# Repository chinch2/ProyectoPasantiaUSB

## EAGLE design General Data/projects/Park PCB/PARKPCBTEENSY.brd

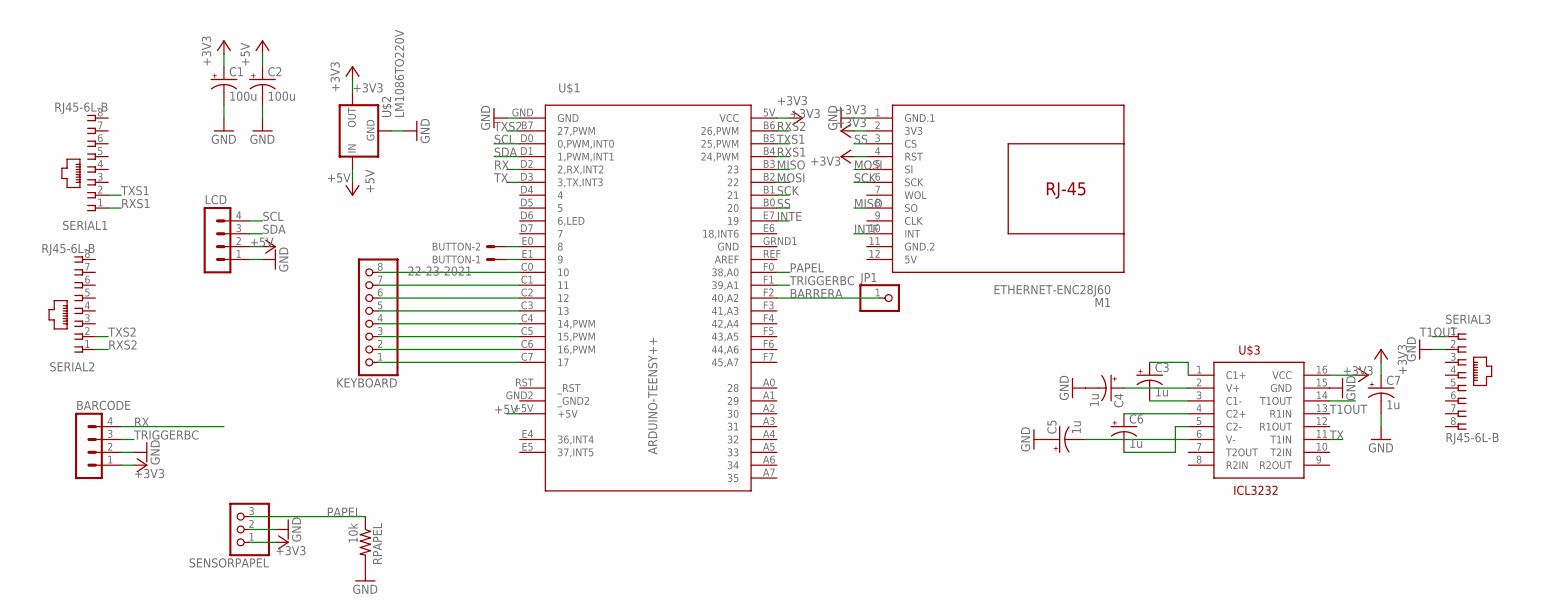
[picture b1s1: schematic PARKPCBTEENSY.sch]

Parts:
BARCODE: MA04-1
BUTTON: 22-23-2021
C1, C2: 100u; B45181B
C3, C4, C5, C6, C7: 1u; B45181B
JP1: PINHD-1X1; 1X01
KEYBOARD: PINHD-1X8BIG; 1X08-BIG
LCD: MA04-1
M1: ETHERNET-ENC28J60
RPAPEL: 10k; 0309/12
SENSORPAPEL: PINHD-1X3; 1X03
SERIAL1, SERIAL2, SERIAL3: RJ45-6L-B; RJ45-NO-SHIELD
U$1: ARDUINO-TEENSY++; TEENSY++
U$2: LM1086TO220V; TO220S
U$3: ICL3232; DIL16

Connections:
5V: M1.12 (5V)
+3V3: BARCODE.1, C1.+, C7.+, M1.2 (3V3), M1.4 (RST), SENSORPAPEL.1, U$1.5V (VCC), U$2.2 (OUT), U$3.16 (VCC)
+5V: C2.+, LCD.2, U$1.+5V, U$2.3 (IN)
BARRERA: JP1.1, U$1.F2 (40,A2)
GND: BARCODE.2, C1.-, C2.-, C4.-, C5.+, C7.-, LCD.1, M1.1 (GND.1), RPAPEL.2, SENSORPAPEL.2, SERIAL3.2, U$1.GND, U$1.GRND1 (GND), U$2.1 (GND), U$3.15 (GND)
GND.2: M1.11 (GND.2)
INTE: M1.10 (INT), U$1.E7 (19)
MISO: M1.8 (SO), U$1.B3 (23)
MOSI: M1.5 (SI), U$1.B2 (22)
unnamed: BUTTON.1, U$1.E1 (9)
unnamed: BUTTON.2, U$1.E0 (8)
unnamed: KEYBOARD.1, U$1.C7 (17)
unnamed: KEYBOARD.2, U$1.C6 (16,PWM)
unnamed: KEYBOARD.3, U$1.C5 (15,PWM)
unnamed: KEYBOARD.4, U$1.C4 (14,PWM)
unnamed: KEYBOARD.5, U$1.C3 (13)
unnamed: KEYBOARD.6, U$1.C2 (12)
unnamed: KEYBOARD.7, U$1.C1 (11)
unnamed: KEYBOARD.8, U$1.C0 (10)
unnamed: C3.+, U$3.1 (C1+)
unnamed: C4.+, U$3.2 (V+)
unnamed: C3.-, U$3.3 (C1-)
unnamed: C6.+, U$3.4 (C2+)
unnamed: C6.-, U$3.5 (C2-)
unnamed: C5.-, U$3.6 (V-)
PAPEL: RPAPEL.1, SENSORPAPEL.3, U$1.F0 (38,A0)
RX: BARCODE.4, U$1.D2 (2,RX,INT2)
RXS1: SERIAL1.1, U$1.B4 (24,PWM)
RXS2: SERIAL2.1, U$1.B6 (26,PWM)
SCK: M1.6 (SCK), U$1.B1 (21)
SCL: LCD.4, U$1.D0 (0,PWM,INT0)
SDA: LCD.3, U$1.D1 (1,PWM,INT1)
SS: M1.3 (CS), U$1.B0 (20)
T1OUT: SERIAL3.1, U$3.14 (T1OUT)
TRIGGERBC: BARCODE.3, U$1.F1 (39,A1)
TX: U$1.D3 (3,TX,INT3), U$3.11 (T1IN)
TXS1: SERIAL1.2, U$1.B5 (25,PWM)
TXS2: SERIAL2.2, U$1.B7 (27,PWM)
_GND2: U$1.GND2 (_GND2)

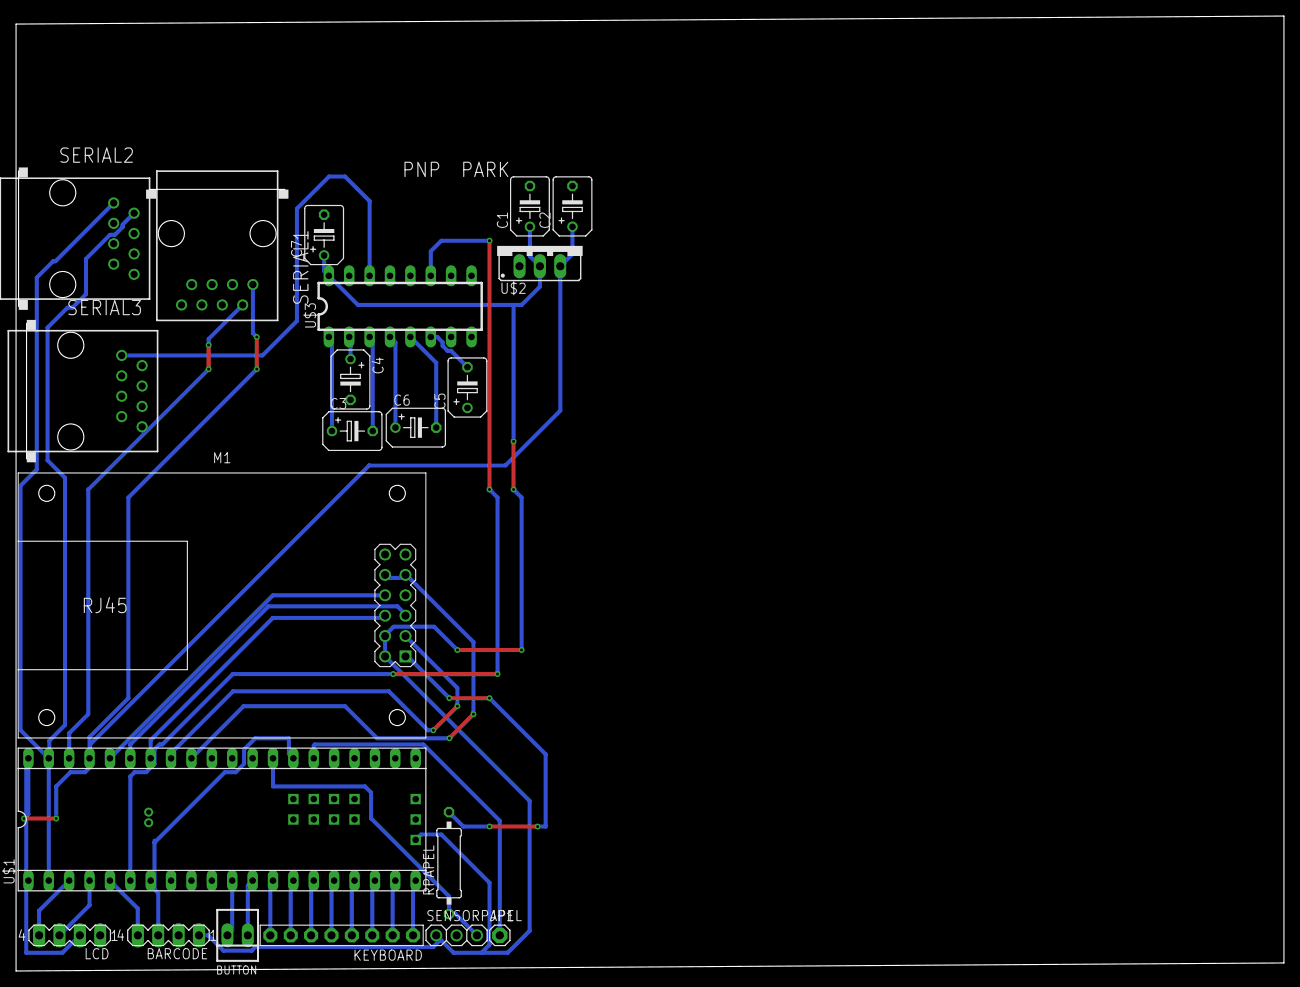
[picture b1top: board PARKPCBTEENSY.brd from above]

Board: 2 copper layers, 158.0 x 119.0 mm, 21 parts (0 on the bottom side), 36 nets.

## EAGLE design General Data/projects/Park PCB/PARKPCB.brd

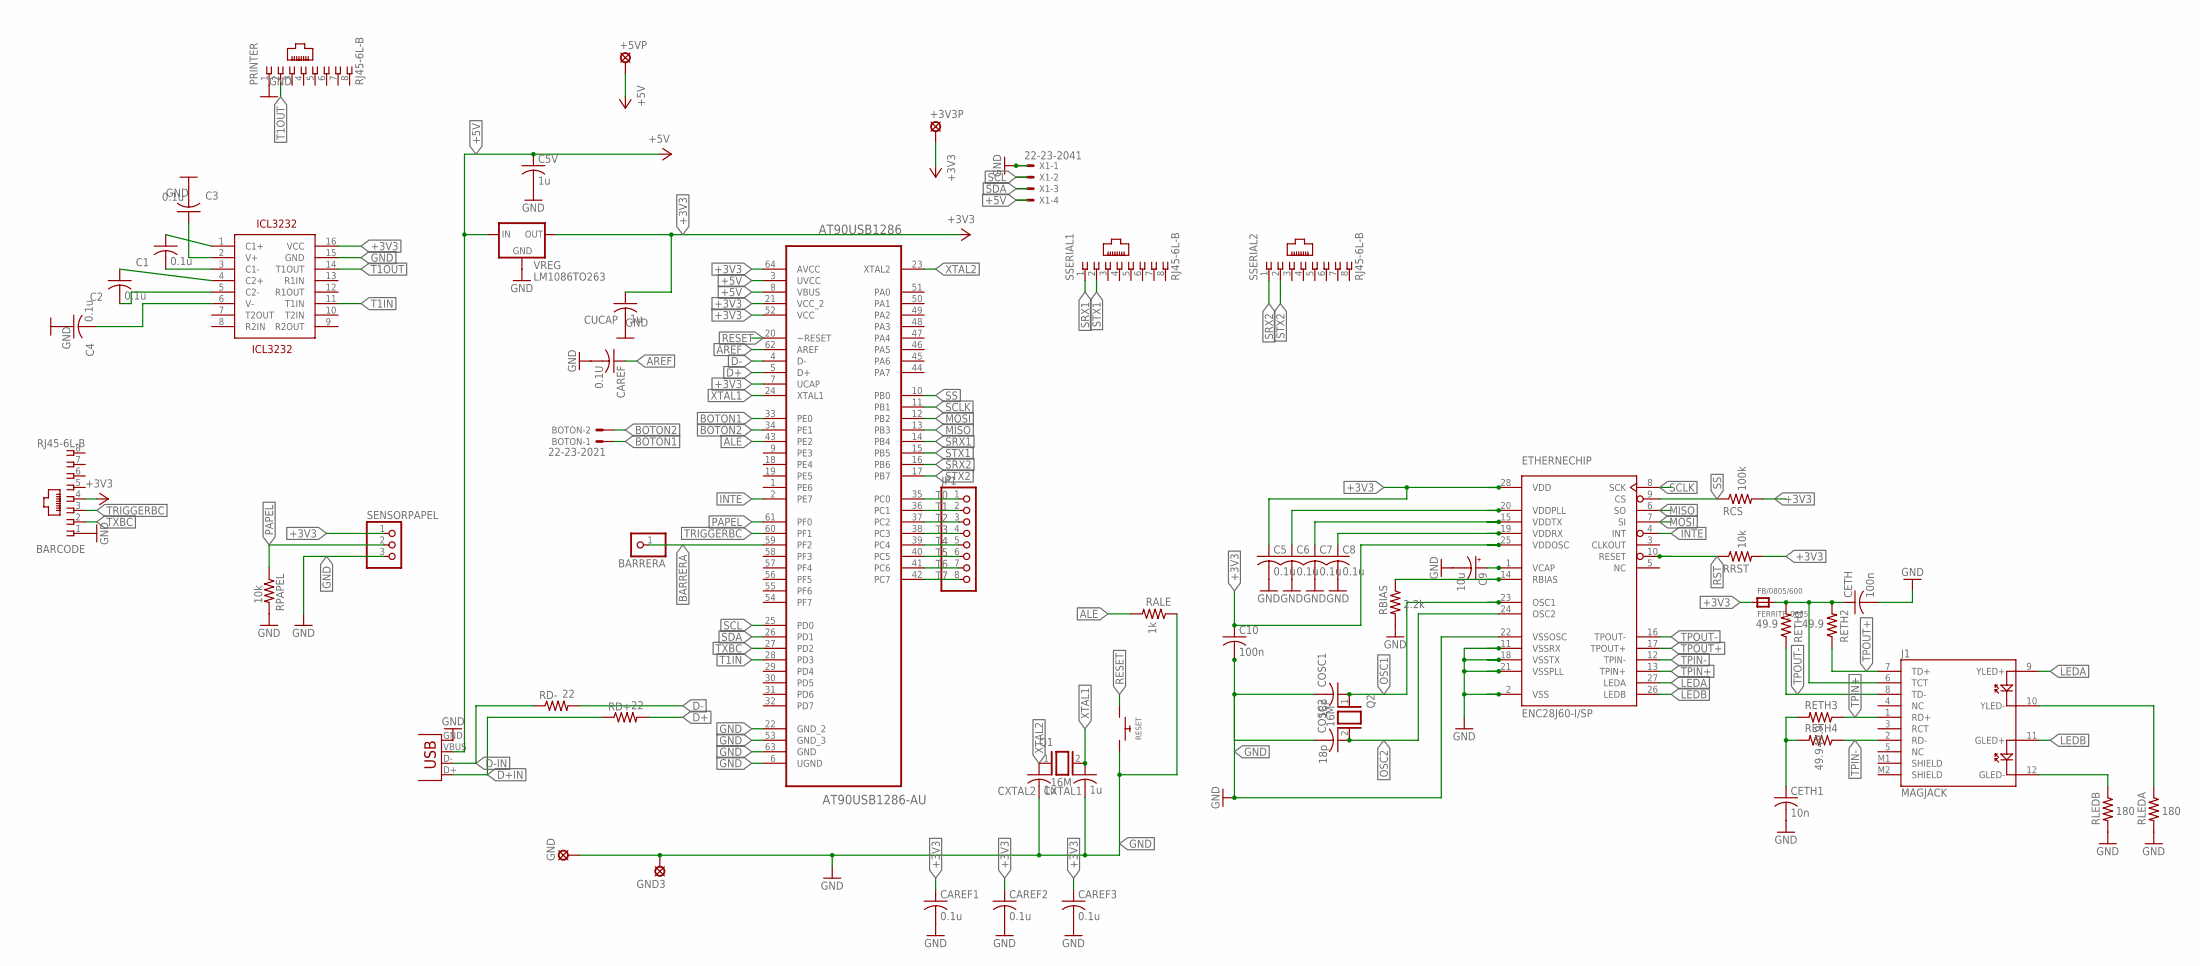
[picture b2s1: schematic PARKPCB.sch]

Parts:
+3V3P, +5VP: LSP10
AT90USB1286: AT90USB1286-AU; QFP80P1600X1600X120-64N
BARCODE: RJ45-6L-B; RJ45-NO-SHIELD
BARRERA: PINHD-1X1; 1X01
BOTON: 22-23-2021
C1, C2, C3, C4, C5, C6, C7, C8: 0.1u; C050-030X075
C5V: 1u; C050-030X075
C9: 10u; B45181B
C10: 100n; C050-030X075
CAREF: 0.1U; C050-030X075
CAREF1, CAREF2, CAREF3: 0.1u; C050-030X075
CETH: 100n; C050-030X075
CETH1: 10n; C050-030X075
COSC1, COSC2: 18p; C050-030X075
CUCAP: 1u; C050-030X075
CXTAL1, CXTAL2: 1u; C050-030X075
ETHERNECHIP: ENC28J60-I/SP; DIP28
FB/0805/600: FERRITE_0805; _0805
GND, GND3: LSP10
ICL3232: ICL3232; DIL16
J1: MAGJACK
JP1: PINHD-1X8BIG; 1X08-BIG
PRINTER: RJ45-6L-B; RJ45-NO-SHIELD
Q1, Q2: 16M; QS
RALE: 1k; 0309/12
RBIAS: 2.2k; 0309/12
RCS: 100k; 0309/12
RD+: 22; 0309/12
RD-: 22; 0309/12
RESET: SWITCH_PUSHBUTTONC&K_KSS; BTN_CK_KSS
RETH1, RETH2, RETH3, RETH4: 49.9; 0309/12
RLEDA: 180; 0309/12
RLEDB: 180; 0309/12
RPAPEL: 10k; 0309/12
RRST: 10k; 0309/12
SENSORPAPEL: PINHD-1X3; 1X03
SSERIAL1, SSERIAL2: RJ45-6L-B; RJ45-NO-SHIELD
USB: USB-MB-S
VREG: LM1086TO263; TO263
X1: 22-23-2041

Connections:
+3V3: +3V3P.MP, AT90USB1286.7 (UCAP), AT90USB1286.21 (VCC_2), AT90USB1286.52 (VCC), AT90USB1286.64 (AVCC), BARCODE.4, C5.1, C10.1, CAREF1.1, CAREF2.1, CAREF3.1, CUCAP.1, ETHERNECHIP.25 (VDDOSC), ETHERNECHIP.28 (VDD), FB/0805/600.1, ICL3232.16 (VCC), RCS.2, RRST.2, SENSORPAPEL.1, VREG.2 (OUT)
+5V: +5VP.MP, AT90USB1286.3 (UVCC), AT90USB1286.8 (VBUS), C5V.1, USB.VBUS, VREG.3 (IN), X1.4
ALE: AT90USB1286.43 (PE2), RALE.2
AREF: AT90USB1286.62 (AREF), CAREF.1
BARRERA: AT90USB1286.59 (PF2), BARRERA.1
BOTON1: AT90USB1286.33 (PE0), BOTON.1
BOTON2: AT90USB1286.34 (PE1), BOTON.2
D+: AT90USB1286.5 (D+), RD+.2
D+IN: RD+.1, USB.D+
D-: AT90USB1286.4 (D-), RD-.2
D-IN: RD-.1, USB.D-
GND: AT90USB1286.6 (UGND), AT90USB1286.22 (GND_2), AT90USB1286.53 (GND_3), AT90USB1286.63 (GND), BARCODE.1, C3.2, C4.1, C5.2, C5V.2, C6.2, C7.2, C8.2, C9.-, C10.2, CAREF.2, CAREF1.2, CAREF2.2, CAREF3.2, CETH.2, CETH1.2, COSC1.2, COSC2.2, CUCAP.2, CXTAL1.2, CXTAL2.2, ETHERNECHIP.2 (VSS), ETHERNECHIP.11 (VSSRX), ETHERNECHIP.18 (VSSTX), ETHERNECHIP.21 (VSSPLL), ETHERNECHIP.22 (VSSOSC), GND.MP, GND3.MP, ICL3232.15 (GND), PRINTER.1, RALE.1, RBIAS.2, RESET.P$2, RLEDA.2, RLEDB.2, RPAPEL.2, SENSORPAPEL.3, USB.GND, VREG.1 (GND), X1.1
INTE: AT90USB1286.2 (PE7), ETHERNECHIP.4 (INT)
LEDA: ETHERNECHIP.27 (LEDA), J1.9 (YLED+)
LEDB: ETHERNECHIP.26 (LEDB), J1.11 (GLED+)
MISO: AT90USB1286.13 (PB3), ETHERNECHIP.6 (SO)
MOSI: AT90USB1286.12 (PB2), ETHERNECHIP.7 (SI)
unnamed: CETH.1, FB/0805/600.2, J1.6 (TCT), RETH1.2, RETH2.2
unnamed: C6.1, ETHERNECHIP.20 (VDDPLL)
unnamed: C7.1, ETHERNECHIP.15 (VDDTX)
unnamed: C8.1, ETHERNECHIP.19 (VDDRX)
unnamed: CETH1.1, RETH3.2, RETH4.2
unnamed: C9.+, ETHERNECHIP.1 (VCAP)
unnamed: ETHERNECHIP.14 (RBIAS), RBIAS.1
unnamed: J1.12 (GLED-), RLEDB.1
unnamed: J1.10 (YLED-), RLEDA.1
unnamed: C1.1, ICL3232.1 (C1+)
unnamed: C3.1, ICL3232.2 (V+)
unnamed: C1.2, ICL3232.3 (C1-)
unnamed: C2.1, ICL3232.4 (C2+)
unnamed: C2.2, ICL3232.5 (C2-)
unnamed: C4.2, ICL3232.6 (V-)
OSC1: COSC1.1, ETHERNECHIP.23 (OSC1), Q2.1
OSC2: COSC2.1, ETHERNECHIP.24 (OSC2), Q2.2
PAPEL: AT90USB1286.61 (PF0), RPAPEL.1, SENSORPAPEL.2
RESET: AT90USB1286.20 (~RESET), RESET.P$1
RST: ETHERNECHIP.10 (RESET), RRST.1
SCL: AT90USB1286.25 (PD0), X1.2
SCLK: AT90USB1286.11 (PB1), ETHERNECHIP.8 (SCK)
SDA: AT90USB1286.26 (PD1), X1.3
SRX1: AT90USB1286.14 (PB4), SSERIAL1.1
SRX2: AT90USB1286.16 (PB6), SSERIAL2.1
SS: AT90USB1286.10 (PB0), ETHERNECHIP.9 (CS), RCS.1
STX1: AT90USB1286.15 (PB5), SSERIAL1.2
STX2: AT90USB1286.17 (PB7), SSERIAL2.2
T0: AT90USB1286.35 (PC0), JP1.1
T1: AT90USB1286.36 (PC1), JP1.2
T1IN: AT90USB1286.28 (PD3), ICL3232.11 (T1IN)
T1OUT: ICL3232.14 (T1OUT), PRINTER.2
T2: AT90USB1286.37 (PC2), JP1.3
T3: AT90USB1286.38 (PC3), JP1.4
T4: AT90USB1286.39 (PC4), JP1.5
T5: AT90USB1286.40 (PC5), JP1.6
T6: AT90USB1286.41 (PC6), JP1.7
T7: AT90USB1286.42 (PC7), JP1.8
TPIN+: ETHERNECHIP.13 (TPIN+), J1.1 (RD+), RETH3.1
TPIN-: ETHERNECHIP.12 (TPIN-), J1.2 (RD-), RETH4.1
TPOUT+: ETHERNECHIP.17 (TPOUT+), J1.7 (TD+), RETH2.1
TPOUT-: ETHERNECHIP.16 (TPOUT-), J1.8 (TD-), RETH1.1
TRIGGERBC: AT90USB1286.60 (PF1), BARCODE.3
TXBC: AT90USB1286.27 (PD2), BARCODE.2
XTAL1: AT90USB1286.24 (XTAL1), CXTAL1.1, Q1.2
XTAL2: AT90USB1286.23 (XTAL2), CXTAL2.1, Q1.1

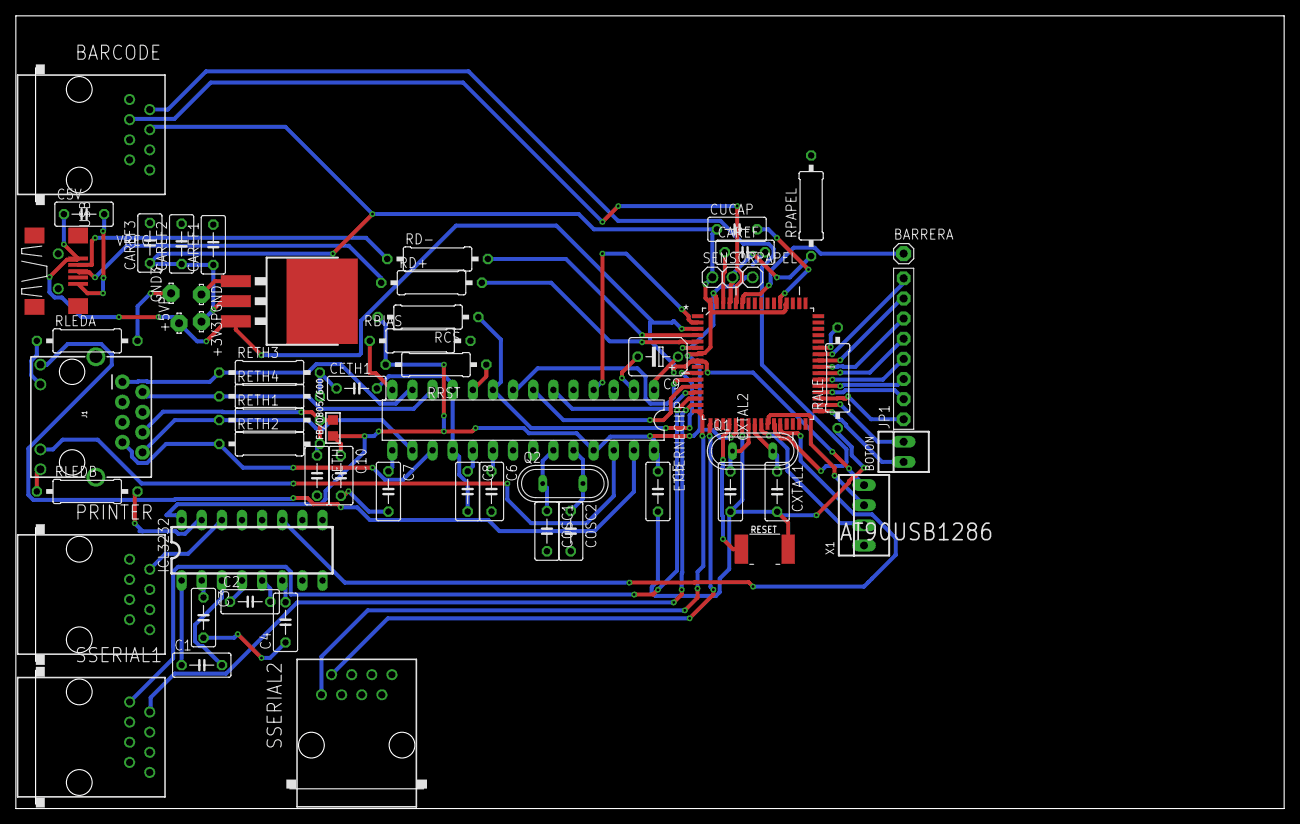
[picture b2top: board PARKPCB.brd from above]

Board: 2 copper layers, 160.0 x 100.0 mm, 58 parts (0 on the bottom side), 63 nets.

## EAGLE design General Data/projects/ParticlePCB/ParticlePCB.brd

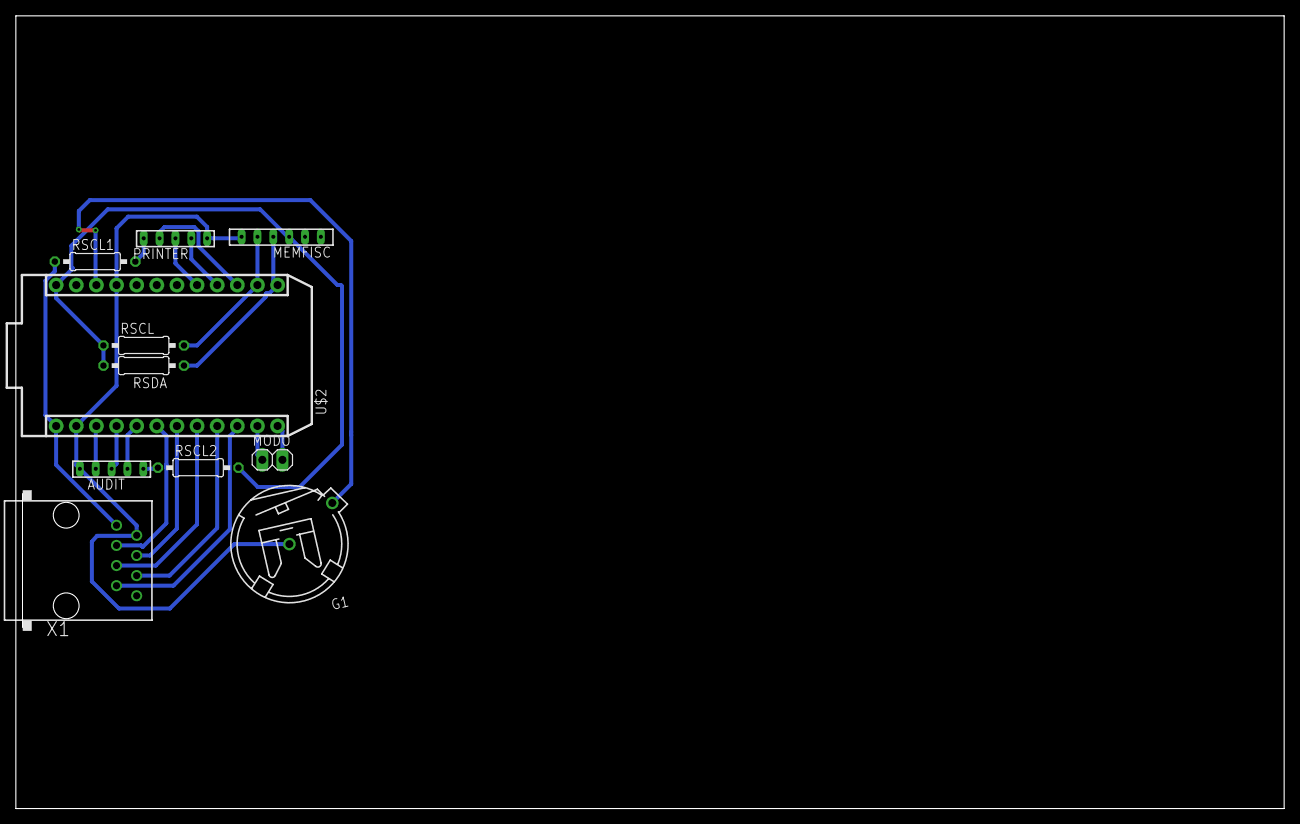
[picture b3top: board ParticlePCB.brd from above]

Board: 2 copper layers, 160.0 x 100.0 mm, 11 parts (0 on the bottom side), 21 nets.

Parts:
AUDIT: 53047-05
G1: CH23-1220LF
MEMFISC: 53047-06
MODO: TECNICO; 1X02
PRINTER: 53047-05
RSCL, RSCL1, RSCL2: 10k; 0207/10
RSDA: 10k; 0207/10
U$2: PHOTON_WITH_HEADERS; PHOTON
X1: RJ45-6L-B; RJ45-NO-SHIELD

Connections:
+3V3: MEMFISC.4, RSCL.1, RSCL2.2, RSDA.2, U$2.24
+5V: RSCL1.1, U$2.1, X1.1
BLK: AUDIT.4, U$2.5
DTR: PRINTER.3, U$2.17
GND: AUDIT.1, G1.-, MEMFISC.1, PRINTER.5, U$2.2, U$2.21, X1.2
MODOTEC0: MODO.2, U$2.12
MODOTEC1: MODO.1, U$2.11
unnamed: PRINTER.1, RSCL1.2
unnamed: AUDIT.5, RSCL2.1
unnamed: U$2.6, X1.3
unnamed: U$2.7, X1.4
unnamed: U$2.8, X1.5
unnamed: U$2.9, X1.6
unnamed: U$2.10, X1.7
RX: AUDIT.3, U$2.4
RXP: PRINTER.2, U$2.15
SCL: MEMFISC.2, RSCL.2, U$2.14
SDA: MEMFISC.3, RSDA.1, U$2.13
TX: AUDIT.2, U$2.3
TXP: PRINTER.4, U$2.16
VBAT: G1.+, U$2.22

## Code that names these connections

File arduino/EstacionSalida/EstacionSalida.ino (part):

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#define tc2 19
#define tc3 20
#define tc4 21
#define papel 24
#define dispara 25
#define barrera 26
#define RXS1 22
#define TXS1 23
#define RXS2 27
#define TXS2 28
#define ss 3

#else //Para teensy++ 2.0
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#define tc2 15
#define tc3 16
#define tc4 17
#define papel 38
#define dispara 39
#define barrera 40
#define RXS1 24
#define TXS1 25
#define RXS2 26
#define TXS2 27
#define ss 20

#endif
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  //Inicializando los pines de entrada y salida
  pinMode(dispara, OUTPUT); //Trigger del escaner
  pinMode(LED, OUTPUT);  //Teensy
  pinMode(barrera, OUTPUT);  //Teensy
  Serial1.println("Botones inicializados");
  Serial.begin(configuracion[1].toInt());
  //inicializo la pantalla
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
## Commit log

2019-01-16 Creación de Branch Arduino
    Creación de la carpeta de prueba y del archivo Arduino en el Branch respectivo.
2019-01-16 Creación de Branch Raspberry
    Creación del branch Raspberry y del archivo de prueba Raspberry.
2019-01-16 Creacion del Branch Arduino
    Creacion del Branch Arduino, Carpeta y archivo
2019-01-16 Me equivoqué creando el branch de arduino
2019-01-16 nueva prueba de arduino
2019-01-16 Prueba de texto en Raspberry
2019-01-16 Creación de código Arduino Estación de Entrada
    Creo el .ino donde voy a empezar a trabajar con la estación de entrada. Código inicial.
2019-01-17 Primer código de Estación de Entrada
    Primera versión de estación de Entrada.
2019-01-17 Cambio de pin de pulsador
2019-01-17 Acomodando el pin de entrada
    Pegando el pin de entrada a una tierra adicional, para que cuando el botón no esté pulsado la salida sea 0 y cuando este pulsado la salida sea 1
2019-01-17 Modificaciones en el código
    De vuelta al INPUT, PULLUP no es lo que se está buscando
2019-01-17 ENTRÓ ALGUIEN!
    Ya funciona la lógica del Arduino. Cuando se activa el lazo por inductancia Y SOLO SI presionan el pulsador se prende un led
2019-01-17 Modificaciones generales de código
2019-01-17 Empezando con el Display
    Se bajó la librería LiquidCrystal_I2C para trabajar con el display dado a las dimensiones dadas, se empezó a escribir el código para éste.
2019-01-17 Primer código de Display
    Primera versión de código de Display
2019-01-17 El Display 20x4 (0x27) funciona
    Falta ahora cambiarlo todo al Display 16x2 (0x3F) pero esto solo cambia haciendo el cambio en LiquidCrystal_I2C lcd(0x3F,16,2);
2019-01-18 Cambios y búsqueda de el display a usar
2019-01-18 Listo el Dispĺay
2019-01-18 Empecé a probar comunicación Serial
2019-01-18 Primer prototipo de ESP8266
2019-01-21 Comentando PtoSerial
    No es necesario por ahora...
2019-01-21 Chao Arduino Hola Teensy
    Mudados completamente a Teensy
2019-01-21 Bienvenido Teensy
2019-01-22 Buscando el led y HablarConESP
    No se consiguió el led. Programa para escribirle al ESP y hablar con él.
2019-01-22 El código del ESP está bien escrito
    El código para el ESP compila... Se hicieron algunos retoques y orden al código
2019-01-24 El led SÍ está en el pin 11
    Estoy cambiando a un teensy que sí le sirve el led.. este no sirve
2019-01-25 ESP FUNCIONA!!!!!
2019-01-25 ESP FUNCIONA PARTE 1
2019-01-27 Acomodando los gets
    Fusionando ESP con estación de entrada.
2019-01-28 Apareció el servidor web en la computadora.
    La laptop es un servidor web, se quiere que sea el raspberry, pero por ahora es la laptop para no tener tantos dispositivos conectados.
2019-01-29 Base de datos creada.
    Hay que estar pendiente de la ip del servidor haciendo ifconfig
2019-01-29 base de datos query actualizado
2019-01-30 Buscando como hago para usar la impresora
    Ya toda la base de datos se entiende como funciona. ahora se esta buscando como se imprime en la impresora y como usar softwareserial... newsoftserial no sirvio.
2019-01-30 Adafruit thermal printer y consulta.php
    hay que arreglar algunas cosas...
2019-02-01 Cambiando los pines de los botones de la estacion de entrada
    esto para poder conectar el puerto SPI para el ethernet... el verdadero proposito del proyecto...
2019-02-01 Empece a probar el modulo ethernet... nada sirve...
2019-02-04 Peleando con el Ethernet...
2019-02-05 SIRVIÓ EL ETHERNET!!
    al fin.
2019-02-05 Empezamos con Ethernet!
2019-02-05 Seguimos con Ethernet
2019-02-06 Reorganizando el codigo para que trabaje de una forma mas ordenada
2019-02-06 No tiene por que haber rele en el codigo
2019-02-06 Eliminando rele
2019-02-06 chao rele
2019-02-06 Arreglado botones
2019-02-07 apareció la impresora y llegó imprimiendo de una!!!
    que nivel
2019-02-07 Cuadrando el codigo con la impresora
    La libreria de adafruit thermal printer sirve
2019-02-07 Solo falta hacer el codigo de barra.
    Hay que aprender a hacer el codigo de barra crudo en la impresora.
2019-02-08 Peleando por crear el codigo de barra en crudo.. necesario?
2019-02-11 Base de datos de equipos primera version.
2019-02-11 Parece que ya estoy imprimiendo el codigo de barra...
2019-02-12 TENEMOS TICKET CON CODIGO DE BARRA
    Se esta usando la libreria thermal printer master de la epson tm t88 y le sirve perfecto a la epson tm t90. estamos imprimiendo codigo ITF de 6 caracteres.
2019-02-13 Creando la configuracion inicial y las index y menu en php
    para mostrar las tablas en el servidor que es desde donde realmente el cliente las va a ver.
2019-02-13 Configuracion inicial
2019-02-14 Configuración Inicial
    Tratando de que, si la EEPROM esta vacía, cargarle IPdef, luego hacer un get con la configuracion inicial a esa IPdef, luego de haber hecho este get se compara la IPdef con la IP que trae la configur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
2019-02-14 TRATANDO DE RECUPERAR EL GET
2019-02-15 La impresora no le da la gana de imprimir
    Se esta tratando de ver que se hace con lo de la configuracion.....
2019-02-15 Algo pasa... revisar
2019-02-16 Arreglando algunas cosas del código desde casa
2019-02-18 de alguna manera extraña todo se arregló.
    Quizás era unas comillas dobles que no puse.
2019-02-18 Impresora definitiva: comandos ESC POS
    no mas librerias. Complican el codigo sin necesidad.
2019-02-18 update de codigo
2019-02-20 ESTACION DE PAGO SE UNE
    Casi funciona.. algo falta con el request
2019-02-21 Acomodando EPago para que haga bien el request
2019-02-21 Estacion de pago SIRVE.
2019-02-21 Probando estaciones de pago y entrada
2019-02-22 Código de teclado
2019-02-22 Corrigiendo teclado y estacion pago funciona con boton
2019-02-22 tratando de que el codigo de teclado funcione
2019-02-22 estacion de pago casi lista
    cuando presionas D en el teclado no quiere hacer el get.
2019-02-25 corrigiendo algunos aspectos del codigo
2019-02-25 Estacion de pago
    tratando de que haga lo que tiene que hacer con los get request y el teclado
2019-02-25 algo pasa con teclado...
2019-02-25 Peleando con el teclado, a veces agarra
2019-02-27 Estacion de pago, estacion de entrada, teclado
    Estacion de pago casi funcionando, no usar Pantalla() en estacion de pago. entorpece el codigo.
2019-02-28 Avance considerable en Estacion de pago
    Estamos casi ahi, angel me esta ayudando
2019-02-28 Estacion de pago. modopagoprueba.
    una funcion nueva donde voy probando de a bloques tengo que resolver el problema de que se me cuelga el codigo... posiblemente falta de memoria?
2019-03-01 UPGRADE DE TODO!!! estaicon de pago sirve
    falta actualizar el pago.php y tabla2.php para p[oder mostrar lo que estoy haciendo en pago.php
2019-03-06 Se suma otro teensy y EstacionSalida.
    Ahora tengo que ver como hacer el setup.php. Es lo mas complicado.
2019-03-07 Agregamos EPPROMSETUPprueba y tratando de que funcione
2019-03-12 trabajando desde casa
    En la parte de setupepprom de la configuracion inicial
2019-03-13 Modificaciones en eppromsetup. Moviendo base de datos
2019-03-13 Cambiando bases de datos
2019-03-13 Estacion de pago y salida listas con setup
    falta la de entrada
2019-03-14 Poniendo las esstaciones al dia desde casa
    falta adaptar la pantaala a los cambios de setup.php
2019-03-14 MEGA upgrade de base de datos y php
    falta arreglar unas cosas y essta listo
2019-03-15 Update en estacion de entrada pago y salida
    Se cuadro el setup.php con lo que se quiere configurar, con la impresora y el display la confifguracion no quiso servir. Se agrego la multa a la base de datos.
2019-03-19 Optimizando los 3 codigos principales
    Se simplificaron muchisimas cosas, se elominaron algunos parametros en los codigos de arduino y se agregaron algunas nuevas sentencias en los php.
2019-03-19 Cambiando MAC ADDRESSES
    para poder tener diferentes direcciones IP
2019-03-19 Cambio de pantalla en estacion de entrada y una pequena mejora
2019-03-20 Tratando de incluir el sensor de cercania en la estacion de escaner
2019-03-21 Sensor de cercania de papel listo!
    Ahora falta el de presencia por inductancia.
2019-03-22 Informacion general
    todo lo relacionado a datasheets
2019-03-26 Servidor en raspberry funcionando
    perfecto. falta hacer mas pruebas. empiezo proyecto de rele con el esp8266
2019-03-28 Proyecto del rele con el ESP8266 listo
    falta un circuito que me permita poder disparar un rele de 5V con 3.3V
2019-04-01 Librerias de eagle
    empezamos con el PCB
2019-04-01 PCB esquematico y board
    el board no sirve
2019-04-02 Trabajando en el PCB
2019-04-03 problema de permiso en las carpetas
2019-04-04 Estacion de entrada ahora con Teensy++ 2.0
2019-04-08 proyecto de ESP8266 con MQTT
    ya esta cogiendo forma.
2019-04-09 puerta funcionando
    falta software. Era el NPN lo que faltaba.
2019-04-09 Proyecto de puerta listo con TELEGRAM
    falta modo host y configurarle la red.
2019-04-11 door2bot funcionando a 5V
    listo wifimanager funcionando
2019-04-11 arreglando repo
2019-04-11 Datasheet del esp para doc de door2bot
2019-04-11 treminando el door2bot
2019-04-15 Corrigiendo el door2bot. El servidor se cayo
    Se puso provisionalmente el de la oficina parece que con este nos vamos a quedar aqui.. descubrimos un SONOFF que implementa todo.. ya veremos que haremos con eso
2019-04-15 Agregando pin del rele para la barrera
    en estacion de entrada cuando imprime el ticket (falta con puesto fijo) y en estacion de salida cuando se pagó el ticket y se esta adentro (condicion para poder salir)
2019-04-16 EAGLE FILES
2019-04-17 Arreglando estacion de entrada con puesto fijo.
    falta salida.
2019-04-22 Puesto fijo en estacion de salida
2019-04-25 Estacion de entrada y salida puesto fijo listo
2019-04-25 Pantalla led creado proyecto
2019-04-26 Software de pantalla led
2019-04-26 7 SGEMENGTOS INTERESANTEO
2019-04-29 Reloj de arduino listo
    Falta que este sincronizado con un relon de oscilador
2019-04-29 Actualización de PCBs
2019-05-08 codigo oficialmente adaptado para la evsaduino
    Se desarrollo una nueva placa de desarrollo propia de la empresa la denominamos evsaduino, aqui es donde se van a empezar a adaptar los proyectos futuros y el actual.
2019-05-08 parkpcb
2019-05-08 Codigo corriendo en evsa
    se arreglo el spi no se necesitan los shift levels y ahora falta arreglar un poco la circuiteria
2019-05-16 Actualiazndo PCBs
2019-05-20 Actualizando PCBs
2019-05-20 Actualizando PHP
2019-05-27 Red local montada.
    Ahora no me importa donde esté
2019-05-28 puesto fijo en entrada
    no en salida, ahi si necesito el software serial
2019-06-10 Usuario fijo listo con rfid!!
2019-06-11 Actualizacion pago y salida
    Completamente operativas, arreglado el problema del reinicio.
2019-06-12 salida adaptada al rfid
2019-08-02 Empezando version basica
2019-08-02 cambios en entreda
2019-08-05 metiendo servidor php en pc tecnetos

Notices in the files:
parts and their libraries:
diy-modules: Released under the Creative Commons Attribution 4.0 International License: http://creativecommons.org/licenses/by/4.0
SparkFun-Connectors: Licensing: Creative Commons ShareAlike 4.0 International - https://creativecommons.org/licenses/by-sa/4.0
